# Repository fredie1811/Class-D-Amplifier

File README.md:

# Class D Audio Amplifier

This project involves the design and implementation of a 2-layer PCB for a *Class D audio amplifier* using a *half-bridge topology* and integrated *Bluetooth streaming* via the *MHM-28 module*. The amplifier is capable of driving a speaker with high efficiency using Pulse Width Modulation (PWM), with clean audio recovery using an LC filter.

## 🔧 Features

* Class D half-bridge topology for efficient audio amplification
* Bluetooth audio streaming using MHM-28 module
* PWM generation with TLC555 timer
* Signal conditioning and dead-time control using LM393 and 74HC04
* Gate driving with IRS2113 for high-side and low-side MOSFET control
* LC filter output for analog audio reconstruction
* 2-layer PCB designed in KiCad

## 📐 System Architecture

| Module           | Description                                             |
| ---------------- | ------------------------------------------------------- |
| TLC555 Timer     | Triangle waveform generator for PWM modulation          |
| LM393 Comparator | Converts audio to PWM by comparing input with reference |
| IRS2113          | High/low-side MOSFET driver for half-bridge control     |
| IRLZ44N MOSFETs  | Power stage switches                                    |
| LC Filter        | Reconstructs analog signal from PWM output              |
| MHM-28 Module    | Bluetooth V4.0 A2DP module for wireless audio           |
| LM7805 / LM7812  | Linear regulators for 5V and 12V power rails            |

## 📊 Technical Specifications

| Parameter         | Value                      |
| ----------------- | -------------------------- |
| Supply Voltage    | 12V                        |
| PWM Frequency     | \~200 kHz                  |
| LC Filter Cutoff  | \~38.6 kHz                 |
| Output Power      | \~10–20 W                  |
| Efficiency        | >90%                       |
| PCB Size          | 2-layer board              |
| Bluetooth Support | Yes (MHM-28, stereo input) |

## 🔋 Power Supply

* LM7805: 5V logic rail
* LM7812: 12V gate driver rail
* Capacitive decoupling at regulator input/output

## 📡 Bluetooth Audio Interface

The MHM-28 module supports:

* Bluetooth V4.0 with A2DP
* Stereo analog output
* Easy pin-header integration
* Direct input to comparator stage

## 🎯 Applications

* Portable wireless audio systems
* DIY speaker projects
* Embedded systems with audio output
* Energy-efficient signal amplification

## 🧠 Learnings

* Class D amplifier design theory
* PWM signal processing and dead-time logic
* High-frequency PCB layout techniques
* Filter design and frequency response analysis
* Bluetooth module integration

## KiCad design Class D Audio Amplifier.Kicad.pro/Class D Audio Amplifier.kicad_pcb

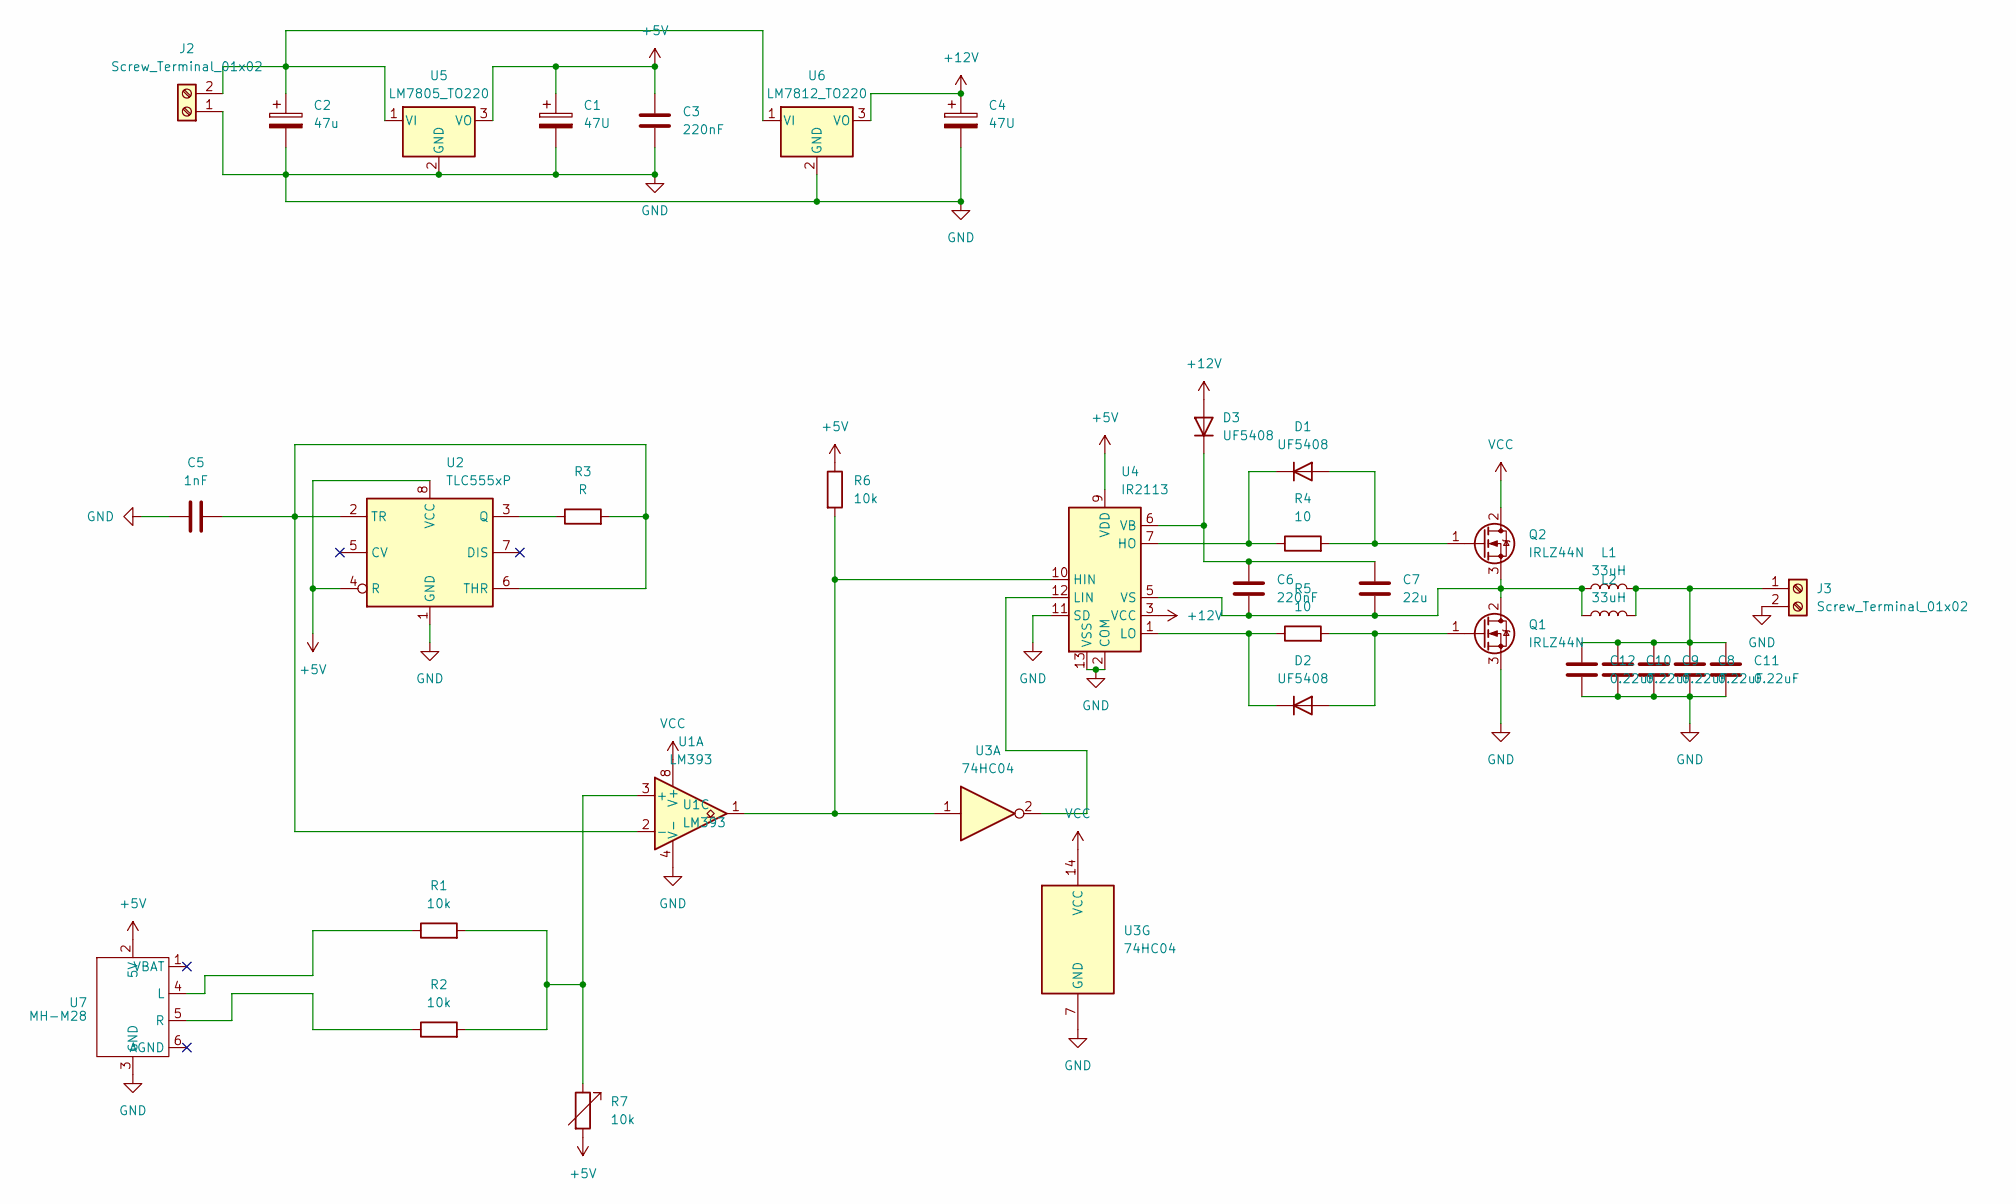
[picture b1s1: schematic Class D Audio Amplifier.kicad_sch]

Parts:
C1, C4: 47U; C_Radial_D5.0mm_H11.0mm_P2.00mm
C2: 47u; C_Radial_D5.0mm_H11.0mm_P2.00mm
C3, C6: 220nF; C_Disc_D4.3mm_W1.9mm_P5.00mm
C5: 1nF; C_Disc_D4.3mm_W1.9mm_P5.00mm
C7: 22u; C_Radial_D5.0mm_H11.0mm_P2.00mm
C8, C9, C10, C11, C12: 0.22uF; C_Rect_L26.5mm_W10.5mm_P22.50mm_MKS4
D1, D2, D3: UF5408; D_DO-201AD_P15.24mm_Horizontal
J2, J3: Screw_Terminal_01x02; TerminalBlock_Phoenix_MKDS-1,5-2-5.08_1x02_P5.08mm_Horizont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
L1, L2: 33uH; L_Radial_D8.7mm_P5.00mm_Fastron_07HCP
Q1, Q2: IRLZ44N; TO-220-3_Vertical
R1, R2, R6, R7: 10k; R_Axial_DIN0204_L3.6mm_D1.6mm_P7.62mm_Horizontal
R3: R; R_Axial_DIN0204_L3.6mm_D1.6mm_P7.62mm_Horizontal
R4, R5: 10; R_Axial_DIN0204_L3.6mm_D1.6mm_P7.62mm_Horizontal
U1: LM393; DIP794W45P254L959H508Q8
U2: TLC555xP; DIP-8_W7.62mm
U3: 74HC04
U4: IR2113; DIP-14_W7.62mm
U5: LM7805_TO220; TO-220-3_Vertical
U6: LM7812_TO220; TO-220-3_Vertical
U7: MH-M28

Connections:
+5V: C1.1, C3.1, R6.1, R7.2, U2.4 (R), U2.8 (VCC), U4.9 (VDD), U5.3 (VO), U7.2 (5V)
+12V: C4.1, D3.2 (A), U4.3 (VCC), U6.3 (VO)
GND: C1.2, C2.2, C3.2, C4.2, C5.1, C8.2, C9.2, C10.2, C11.2, C12.2, J2.1, J3.2, Q1.3 (S), U1.4 (V-), U2.1 (GND), U3.7 (GND), U4.2 (COM), U4.11 (SD), U4.13 (VSS), U5.2 (GND), U6.2 (GND), U7.3 (GND)
unnamed: D1.2 (A), Q2.1 (G), R4.2
unnamed: D1.1 (K), R4.1, U4.7 (HO)
unnamed: D2.2 (A), Q1.1 (G), R5.2
unnamed: D2.1 (K), R5.1, U4.1 (LO)
unnamed: C6.1, C7.1, D3.1 (K), U4.6 (VB)
unnamed: C2.1, J2.2, U5.1 (VI), U6.1 (VI)
unnamed: C8.1, C9.1, C10.1, C11.1, C12.1, J3.1, L1.2, L2.2
unnamed: C6.2, C7.2, L1.1, L2.1, Q1.2 (D), Q2.3 (S), U4.5 (VS)
unnamed: R1.2, R2.2, R7.1, U1.3 (+)
unnamed: C5.2, R3.2, U1.2 (-), U2.2 (TR), U2.6 (THR)
unnamed: R3.1, U2.3 (Q)
unnamed: R6.2, U1.1, U3.1, U4.10 (HIN)
unnamed: U3.2, U4.12 (LIN)
unnamed: R1.1, U7.4 (L)
unnamed: R2.1, U7.5 (R)
VCC: Q2.2 (D), U1.8 (V+), U3.14 (VCC)

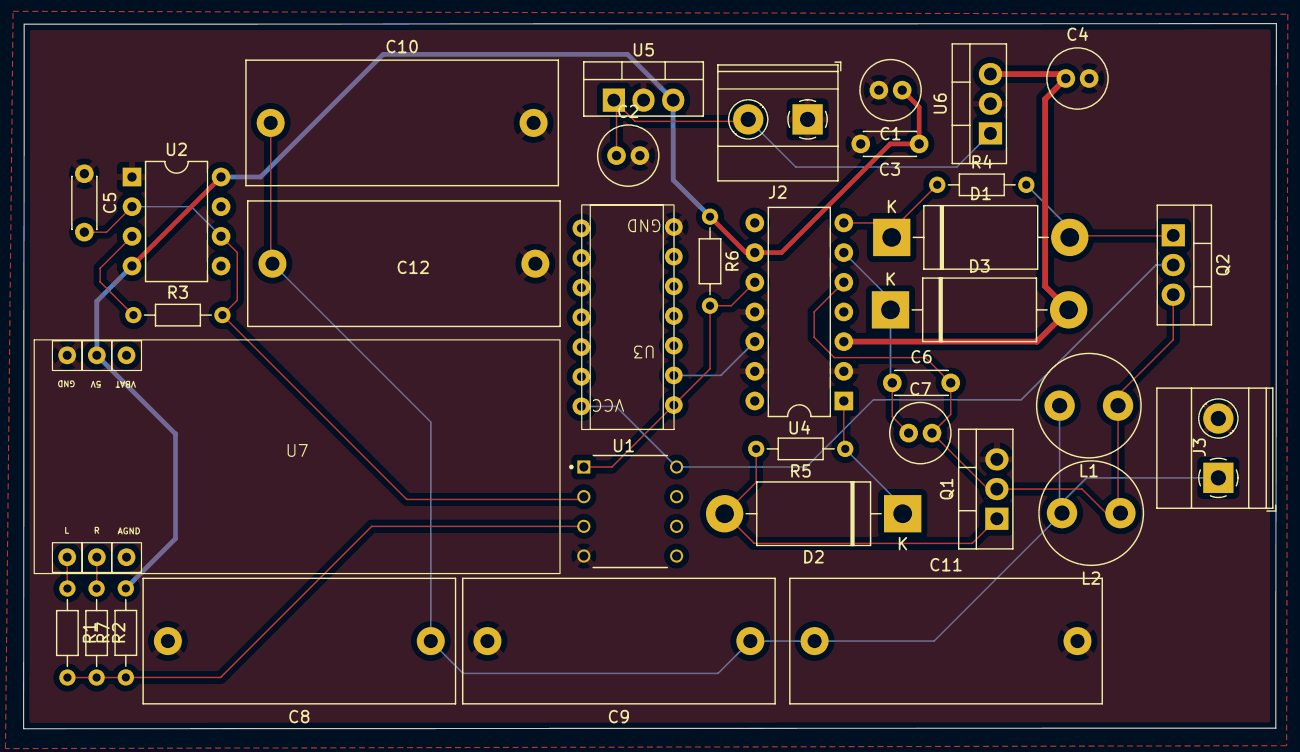
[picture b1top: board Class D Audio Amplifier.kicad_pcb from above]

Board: 2 copper layers, 107.2 x 60.3 mm, 35 parts (0 on the bottom side), 19 nets.
